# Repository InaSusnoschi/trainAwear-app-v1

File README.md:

## Train-A-Wear
### A wearable workout monitor that provides real time feedback on the user's form while performing basic workouts to improve shape and exercise outcomes.

This uses a Raspberry Pi and three Inertial Measurement Units that detect position and orientation of the body segments they are placed on.

## Prerequisites
Inertial Measurement Unit train-box

### Android app:
<ul>
  <li> Android SDK 27 </li>
  <li> Android Build tools v27.0.2 </li>
  <li> Android Support Repository </li>
  <li> compile 'com.synnapps:carouselview:0.1.5' in Gradle file</>
</ul>

## Installing

## Documentation

### Examples
Using IMU data to obtain body position and orientation.

Decision loops for workout feedback.

Real time data plotting on smartphone (php)

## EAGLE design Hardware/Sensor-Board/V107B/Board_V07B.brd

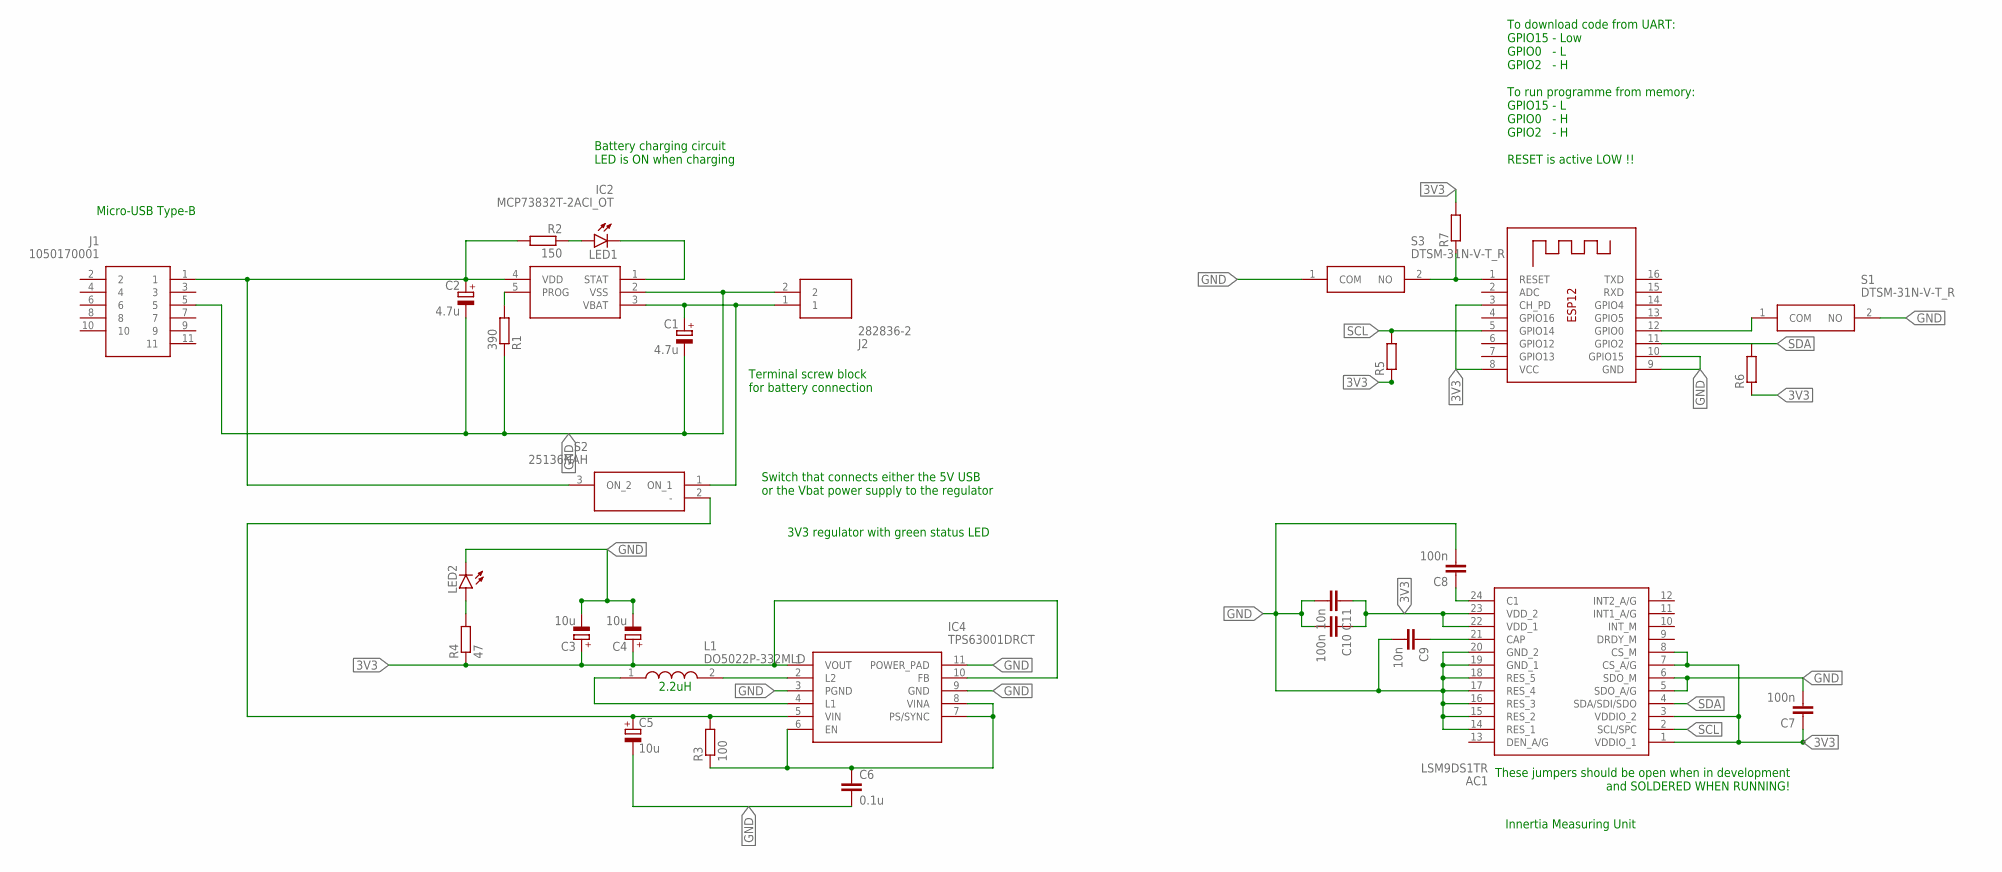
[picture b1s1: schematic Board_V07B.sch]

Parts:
AC1: LSM9DS1TR; LGA-24L(3X3.5X1MM)
C1, C2: 4.7u; D/7343-31R
C3, C4, C5: 10u; D/7343-31R
C6: 0.1u; C0402
C7, C8, C10: 100n; C0805
C9, C11: 10n; C0805
IC2: MCP73832T-2ACI_OT; SOT95P270X145-5N
IC4: TPS63001DRCT; SON50P300X300X100-11N
J1: 1050170001; MICROUSB-BTYPE
J2: 282836-2; SHDR2W100P0X500_1X2_1000X820X1
L1: DO5022P-332MLD; DO5022P-104MLD
LED1, LED2: LED5MM
R1: 390; R0805
R2: 150; R0805
R3: 100; R0805
R4: 47; R0805
R5, R6, R7: R-EU_R0805; R0805
S1, S3: DTSM-31N-V-T_R; DTSM32NVTR
S2: 25136NAH
X1: ESP-12

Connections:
3V3: AC1.1 (VDDIO_1), AC1.3 (VDDIO_2), AC1.7 (CS_A/G), AC1.8 (CS_M), AC1.22 (VDD_1), AC1.23 (VDD_2), C3.+, C4.+, C7.1, C10.1, C11.1, IC4.1 (VOUT), IC4.10 (FB), R4.1, R5.1, R6.1, R7.2, X1.3 (CH_PD), X1.8 (VCC)
5V: C2.+, IC2.4 (VDD), J1.1, R2.2, S2.3 (ON_2)
GND: AC1.5 (SDO_A/G), AC1.6 (SDO_M), AC1.14 (RES_1), AC1.15 (RES_2), AC1.16 (RES_3), AC1.17 (RES_4), AC1.18 (RES_5), AC1.19 (GND_1), AC1.20 (GND_2), C1.-, C2.-, C3.-, C4.-, C5.-, C6.2, C7.2, C8.2, C9.2, C10.2, C11.2, IC2.2 (VSS), IC4.3 (PGND), IC4.9 (GND), IC4.11 (POWER_PAD), J1.5, J2.2, LED2.K (C), R1.1, S1.2 (NO), S3.1 (COM), X1.9 (GND), X1.10 (GPIO15)
unnamed: IC2.5 (PROG), R1.2
unnamed: LED1.A, R2.1
unnamed: AC1.21 (CAP), C9.1
unnamed: C5.+, IC4.5 (VIN), R3.2, S2.2 (-)
unnamed: LED2.A, R4.2
unnamed: IC4.2 (L2), L1.2
unnamed: IC4.4 (L1), L1.1
unnamed: C6.1, IC4.6 (EN), IC4.7 (PS/SYNC), IC4.8 (VINA), R3.1
unnamed: AC1.24 (C1), C8.1
unnamed: S1.1 (COM), X1.12 (GPIO0)
unnamed: R7.1, S3.2 (NO), X1.1 (RESET)
SCL: AC1.2 (SCL/SPC), R5.2, X1.5 (GPIO14)
SDA: AC1.4 (SDA/SDI/SDO), R6.2, X1.11 (GPIO2)
STAT: IC2.1 (STAT), LED1.K (C)
VBAT: C1.+, IC2.3 (VBAT), J2.1, S2.1 (ON_1)

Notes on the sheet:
Micro-USB Type-B
Battery charging circuit LED is ON when charging
Terminal screw block for battery connection
3V3 regulator with green status LED
Switch that connects either the 5V USB or the Vbat power supply to the regulator
Innertia Measuring Unit
These jumpers should be open when in development and SOLDERED WHEN RUNNING!
2.2uH
To download code from UART: GPIO15 - Low GPIO0 - L GPIO2 - H To run programme from memory: GPIO15 - L GPIO0 - H GPIO2 - H RESET is active LOW !!

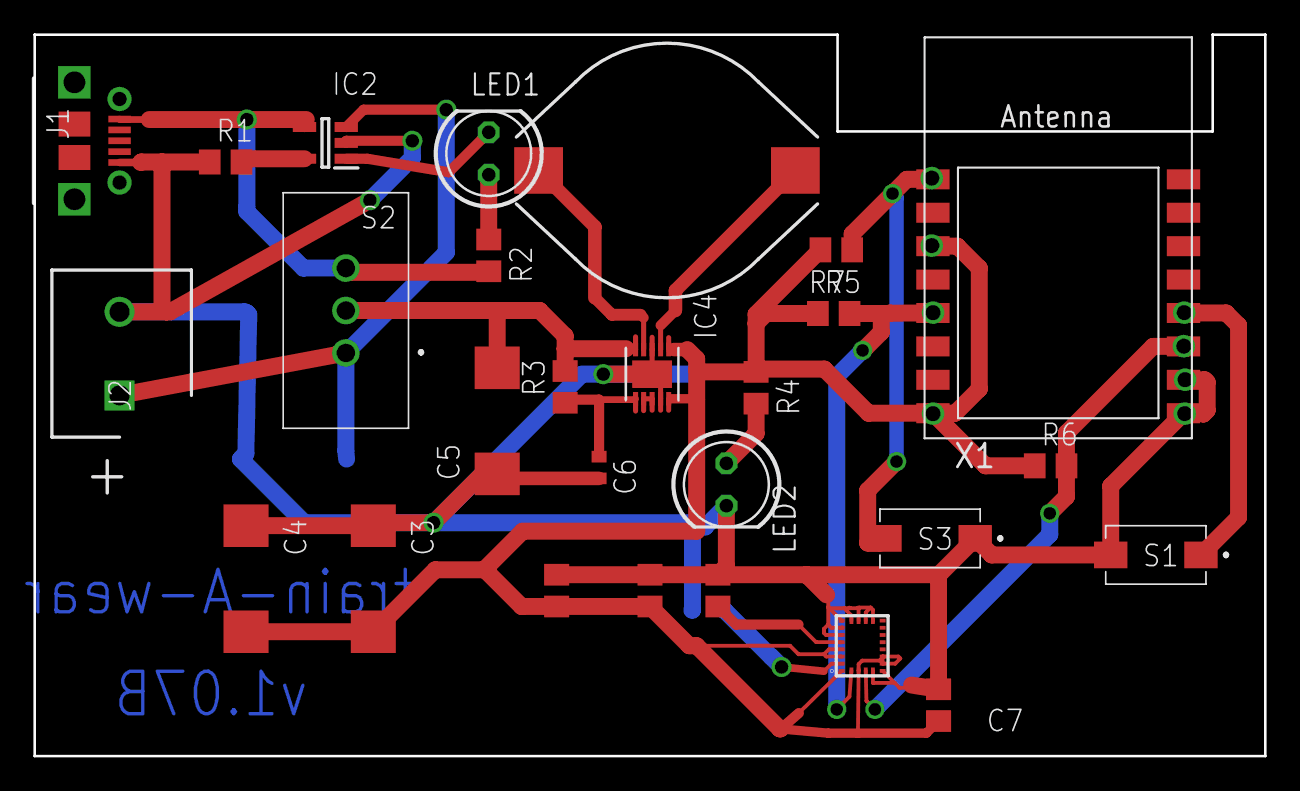
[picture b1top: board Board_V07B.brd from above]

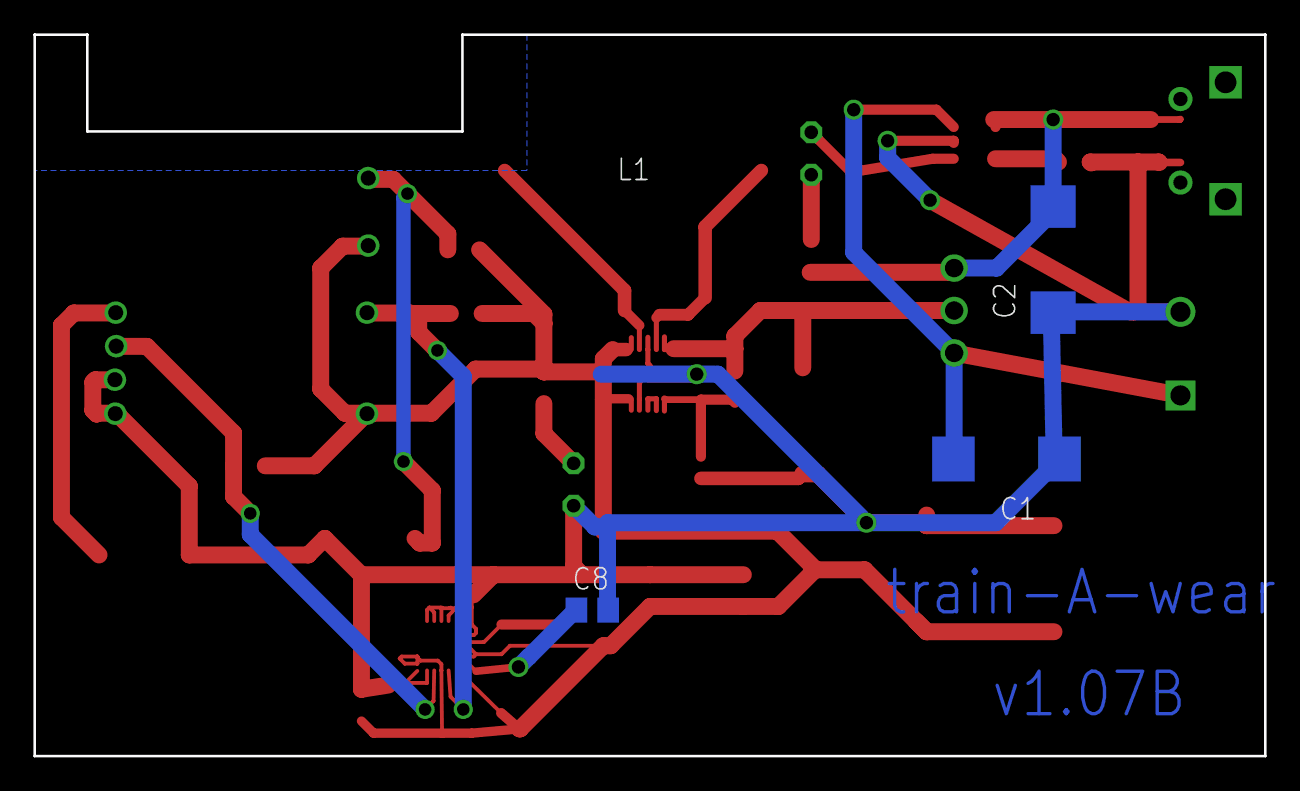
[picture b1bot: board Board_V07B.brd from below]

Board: 2 copper layers, 73.7 x 43.2 mm, 30 parts (3 on the bottom side), 18 nets.

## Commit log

2019-01-30 Uploading the presentation for the pitch
2019-02-19 Add files via upload
    User stories used when developing the Android Application and the algorithm
2019-02-19 Add files via upload
    Our logo!
2019-02-19 Add files via upload
    A sample of how to use the sensors to get personalised feedback on your squats
2019-02-19 Create AndroidApp0.1-Start activity
    The start activity of the Android app for trainAwear
2019-02-19 Create Activity1-Main
2019-02-19 Rename Activity1-Main to Activity1-Main v0.1
    First version, XML done with drag&drop
2019-02-19 Rename Activity1-Main v0.1 to Main-dependencies
    Main activity dependencies
2019-03-01 Added initial schematics and PCB for board version 1.2
2019-03-01 Added images for the schematic and PCB to facilitate inspection on systems without appropriate software.
2019-03-01 Added V1.03 for the hardware of the sensor.
2019-03-01 Added version 1.4 of the board along with hand-traced PCB.
2019-03-01 Added latest hardware version - 1.05 which has also been manufactured.
2019-03-01 Added PCB image to description 1.05
2019-03-01 Added schematic image too to the readme for V105.
2019-03-02 Added Bill of Materials for current board version.
2019-03-02 Added datasheets for all ICs on the board and microUSB connector.
2019-03-02 Added logo main Readme file.
2019-03-02 Cleaned up the Readme file from previous commit.
    Replaced title of the project with centered logo.
2019-03-06 Add files via upload
    Side view soldering the IMU (microscope 40X)
2019-03-14 Create tests
2019-03-17 Add files via upload
    Component Diagram of the Train-A-Wear wearable system
2019-03-20 Create App-v-1
2019-04-04 Added datasheets for the two new microcontrollers to be used for the sensor.
2019-04-04 Added next board version based on WROOM-02. Removed programming headers for simplicity of the board and added holes for P&P capability of the mcu.
2019-04-04 Added board based on ESP8266 module ESP-12.
2019-04-06 UDP connection and server
2019-04-06 Added doxygen file
2019-04-06 Doxygen file - not empty this time
2019-04-06 Added initial software skeleton for the sensor microcontroller code. Based on Arduino dev environment and not on pure toolchain.
2019-04-06 Added some doc referencing for used libraries.
2019-04-07 Added functionality that connects to the strongest WiFi AP. Changed some function signatures to improve usability.
2019-04-08 Additional functionality - send messages to client until disconnect
2019-04-08 Added STL files for the sensor box by Maggie.
2019-04-08 Modified serial speed to match the speed of the debug serial so there is no need to switch between them.
2019-04-09 Sensor software now waits for server transmission to identify server IP address. SendUDP tested nand working!
2019-04-10 Added an extra print line for easier debugging.
2019-04-10 Improved consistency of handshake text across clients and server. Reduced hardcoded values.
2019-04-10 AI-3.3 <ioana@DESKTOP-HQ4826F Overwrite remote https://github.com/InaSusnoschi/train-A-wear.git to local
2019-04-10 AI-3.3 <ioana@DESKTOP-HQ4826F Create git.xml, project.default.xml, laf.xml, other.xml, jdk.table.xml, Default.xml, path.macros.xml, androidStudioFirstRun.xml, find.xml, ui.lnf.xml, filetypes.xml, vcs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
2019-04-10 Create UDPClient-AndroidApp
2019-04-10 AI-3.3 <ioana@DESKTOP-HQ4826F Delete other.xml, jdk.table.xml
2019-04-17 Create doc
    this will host the documentation
2019-04-17 documentation for App
2019-04-17 html documentation folder
2019-04-17 First page commit
2019-04-18 added html doc to .gitignore
2019-04-18 Added all the html documentation
2019-04-18 readded html doc
2019-04-18 App docs
